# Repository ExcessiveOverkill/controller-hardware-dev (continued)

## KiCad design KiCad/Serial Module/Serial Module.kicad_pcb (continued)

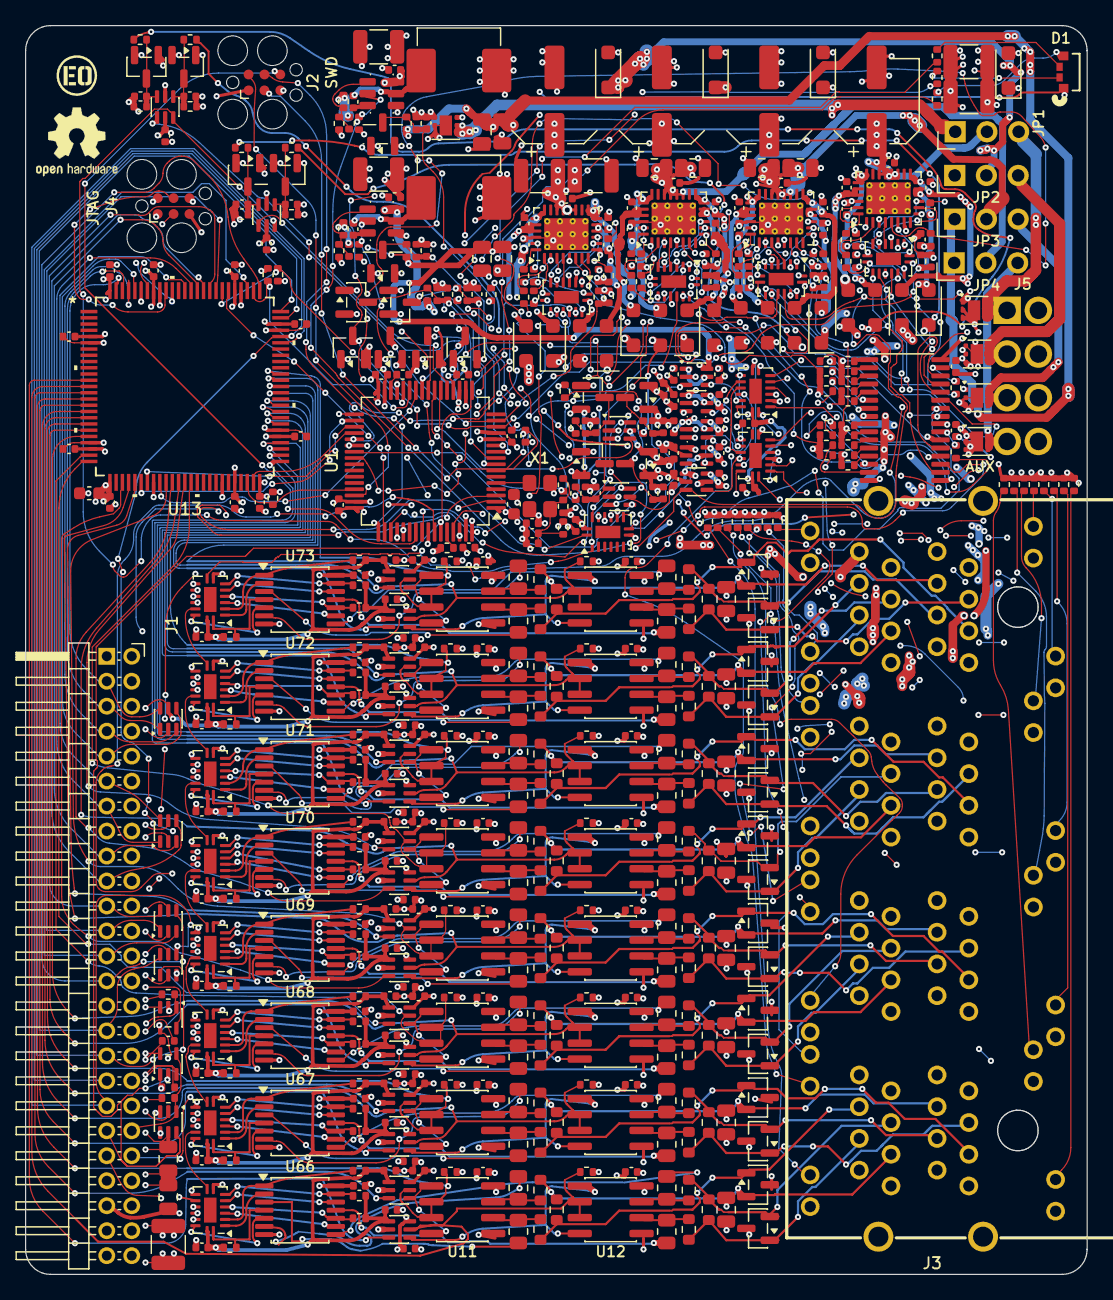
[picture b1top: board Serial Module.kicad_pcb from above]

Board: 4 copper layers, 85.0 x 100.0 mm, 564 parts (0 on the bottom side), 454 nets.

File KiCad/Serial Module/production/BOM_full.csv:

"Designator","Value","Footprint","Part number","Manufacturer","LCSC#","Qty","DNP"
"C1","4.7uf","Capacitor_SMD:C_0402_1005Metric","CC0402MRX5R6BB475","YAGEO","C469468","1",""
"C2,C4-C10,C15-C19,C25-C27,C30-C33,C38,C42,C43,C52,C53,C60-C67,C69-C88,C96-C109,C111-C113,C117-C131,C133,C134,C138,C139,C145-C152,C157,C158,C160-C165,C167-C172,C174-C188",".1uf","Capacitor_SMD:C_0402_1005Metric","CC0402KRX7R9BB104","YAGEO","C131394","126",""
"C3,C68","4.7uf","Capacitor_SMD:C_0603_1608Metric","CC0603KRX5R7BB475","YAGEO","C277476","2",""
"C11,C12,C46-C49,C115,C116,C136,C137,C140-C144,C159,C166,C173","22uf","Capacitor_SMD:C_0805_2012Metric","CC0805MKX5R8BB226","YAGEO","C784585","18",""
"C13,C24,C28,C35,C36,C110,C132","10uF","Capacitor_SMD:C_1210_3225Metric","CC1210KKX7R9BB106","YAGEO","C596319","7",""
"C14","2.2uf","Capacitor_SMD:C_0402_1005Metric","CC0402KRX5R6BB225","YAGEO","C326606","1",""
"C20-C23,C37,C39-C41,C50,C51,C54-C59","22nf","Capacitor_SMD:C_0402_1005Metric","CC0402KRX7R9BB223","YAGEO","C107026","16",""
"C29,C34,C44,C45","100uF","Capacitor_SMD:CP_Elec_6.3x7.7","JVJ50V100M6x8","jieerrui","C46550415","4",""
"C153-C156","10nf","Capacitor_SMD:C_0402_1005Metric","CC0402KRX7R9BB103","YAGEO","C60133","4",""
"D1","22-23C","footprints:22-23C_EVE","22-23C/R6GHBHW-C01/2C","Everlight","C181865","1",""
"D3,D4,D28-D35,D50-D55","BAT54SLT1G","Package_TO_SOT_SMD:SOT-23","LBAT54SLT1G","LRC","C12765","16",""
"D6,D7,D36-D49","SM712_SOT23","Package_TO_SOT_SMD:SOT-23","SM712","MDD(Microdiode Semiconductor)","C502564","16",""
"D8-D27","D_Schottky","Diode_SMD:D_SOD-123F","K24","GOODWORK","C908664","20",""
"D56,D57","TVS2700","Package_SON:WSON-6-1EP_2x2mm_P0.65mm_EP1x1.6mm","TVS2700DRVR","TI","C523797","2",""
"J1","Conn_02x25_Odd_Even","footprints:16x_modular_card","X4621WR-2x25I-C40D28","XKB Connection","C2883281","1",""
"J3","","footprints:RJ45-TH_HC-RJ45-059D-2X4-2-04","HC-RJ45-059D-2*4-2-04","HCTL","C46261621","1",""
"J5","Conn_02x04_Odd_Even","footprints:2x04_P3.5_KF2EDGSR","KF2EDGSR-3.5-2*4P","Cixi Kefa Elec","C2923262","1",""
"JP1-JP4","Jumper_3_Bridged12","footprints:PinHeader_1x03_P2.54mm_Vertical_Shunt12","PZ254V-11-03P","XFCN","C2937625","4",""
"JS1-JS4","Shunt 2.54mm","","2.54Short Circuit Cap Closed","BOOMELE","C100114","4",""
"L1,L5","6.8uH","Inductor_SMD:L_Changjiang_FXL0650","FXL0650-6R8-M","cjiang (Changjiang Microelectronics)","C475530","2",""
"R1,R2,R6,R8,R9,R30,R32,R34,R36,R38,R40,R42,R44,R256,R270,R287,R288","1k","Resistor_SMD:R_0402_1005Metric","RC0402FR-071KL","YAGEO","C106235","17",""
"R3-R5,R7,R24-R29,R31,R33,R35,R37,R39,R41,R43,R61-R63,R160,R161,R243,R244,R247,R248,R353-R421","10k","Resistor_SMD:R_0402_1005Metric","RC0402FR-0710KL","YAGEO","C60490","95",""
"R14-R17,R45-R60,R64-R67,R74-R77,R84-R87,R94-R97,R104-R107,R114-R117,R124-R127","470","Resistor_SMD:R_0402_1005Metric","RC0402FR-07470RL","YAGEO","C114877","48",""
"R18-R21,R68-R71,R78-R81,R88-R91,R98-R101,R108-R111,R118-R121,R128-R131","10","Resistor_SMD:R_0402_1005Metric","RC0402FR-0710RL","YAGEO","C138066","32",""
"R22,R23,R72,R73,R82,R83,R92,R93,R102,R103,R112,R113,R122,R123,R132,R133","137","Resistor_SMD:R_0603_1608Metric","0603WAF1370T5E","UNI-ROYAL","C22873","16",""
"R162,R245","100k","Resistor_SMD:R_0402_1005Metric","RC0402FR-07100KL","YAGEO","C60491","2",""
"R163","12.4k","Resistor_SMD:R_0402_1005Metric","RC0402FR-0712K4L","YAGEO","C138060","1",""
"R246","13.3k","Resistor_SMD:R_0402_1005Metric","RC0402FR-0713K3L","YAGEO","C274352","1",""
"R249-R252","330","Resistor_SMD:R_0402_1005Metric","RC0402FR-07330RL","YAGEO","C105875","4",""
"R253,R257,R262,R264,R271,R272,R275,R276","8.06k","Resistor_SMD:R_0402_1005Metric","RC0402FR-078K06L","YAGEO","C276278","8",""
"R254,R266,R279,R280","4.02k","Resistor_SMD:R_0402_1005Metric","RC0402FR-074K02L","YAGEO","C137968","4",""
"R255,R268,R283,R284","2k","Resistor_SMD:R_0402_1005Metric","RC0402FR-072KL","YAGEO","C60488","4",""
"U1","STM32F411RETx","Package_QFP:LQFP-64_10x10mm_P0.5mm","STM32F411RET6","STMicroelectronics","C94355","1",""
"U2-U6","D1213A-04S-7","Package_TO_SOT_SMD:SOT-363_SC-70-6","D1213A-04S-7-ES","ElecSuper","C41409235","5",""
"U7,U8","74LVC1G126","Package_TO_SOT_SMD:SOT-353_SC-70-5","74LVC1G126CT05ARCQ","GR","C48391411","2",""
"U9,U10,U16,U17,U28,U29,U32,U33,U36,U37,U40,U41,U44,U45,U48,U49,U88-U92","SN74LVC1T45DCK","Package_TO_SOT_SMD:SOT-363_SC-70-6","SN74LVC1T45DCKR","TI","C9382","21",""
"U11,U12,U26,U27,U30,U31,U34,U35,U38,U39,U42,U43,U46,U47,U50,U61","THVD1420DRL","Package_TO_SOT_SMD:SOT-583-8","THVD1420DRLR","TI","C3235555","16",""
"U13","LCMXO2-640HC-4TG100I","footprints:TQFP100_LAT","LCMXO2-640HC-4TG100I","Lattice","C5680157","1",""
"U14,U18,U20,U21,U51-U60,U84","74HC595","Package_DFN_QFN:DHVQFN-16-1EP_2.5x3.5mm_P0.5mm_EP1x2mm","74HC595BQ,115","Nexperia","C730243","15",""
"U15,U19,U22,U23","TPS274160BRLHR","Package_DFN_QFN:VQFN-28-1EP_4x5mm_P0.5mm_EP2.55x3.55mm_ThermalVias","TPS274160BRLHR","TI","C2797257","4",""
"U24,U25","74HCS596","Package_SO:TSSOP-16_4.4x5mm_P0.65mm","SN74HCS596QPWRQ1","TI","C2862662","2",""
"U65,U82","LMR51420YFDDCR","Package_TO_SOT_SMD:SOT-23-6","LMR51420YFDDCR","TI","C7296200","2",""
"U66-U73","74ACT125","Package_SO:TSSOP-14_4.4x5mm_P0.65mm","SN74ACT125PWR","TI","C52940839","8",""
"U83,U85-U87","74LVC1G3157","Package_TO_SOT_SMD:SOT-363_SC-70-6","SN74LVC1G3157DCKR","TI","C38663","4",""
"X1","25Mhz","Oscillator:Oscillator_SMD_Abracon_ASE-4Pin_3.2x2.5mm","SX3V25.000B20100F30TNN","SCTF","C5179998","1",""

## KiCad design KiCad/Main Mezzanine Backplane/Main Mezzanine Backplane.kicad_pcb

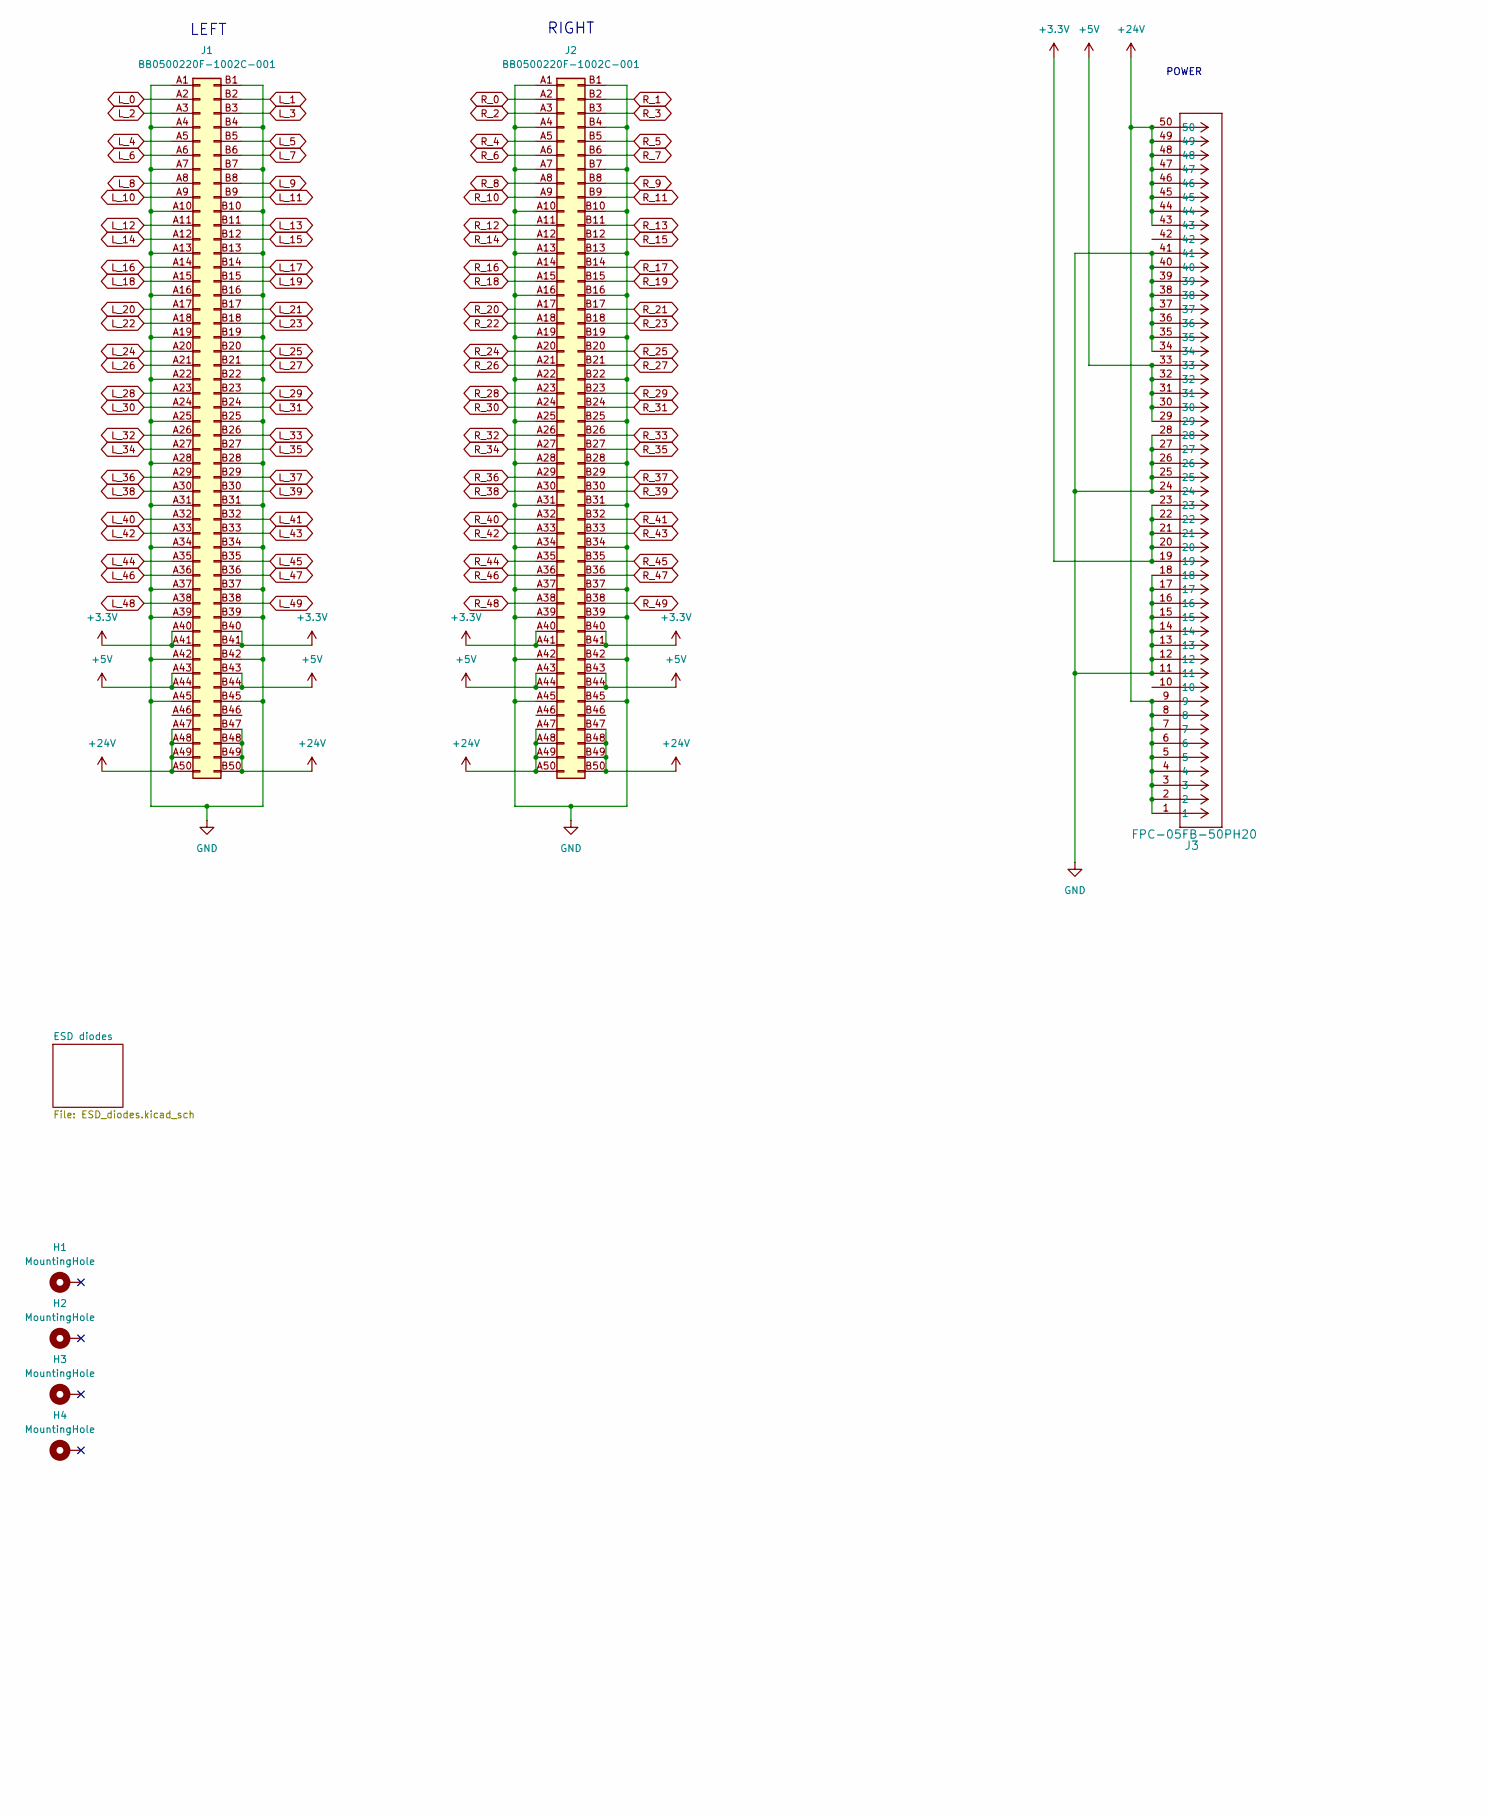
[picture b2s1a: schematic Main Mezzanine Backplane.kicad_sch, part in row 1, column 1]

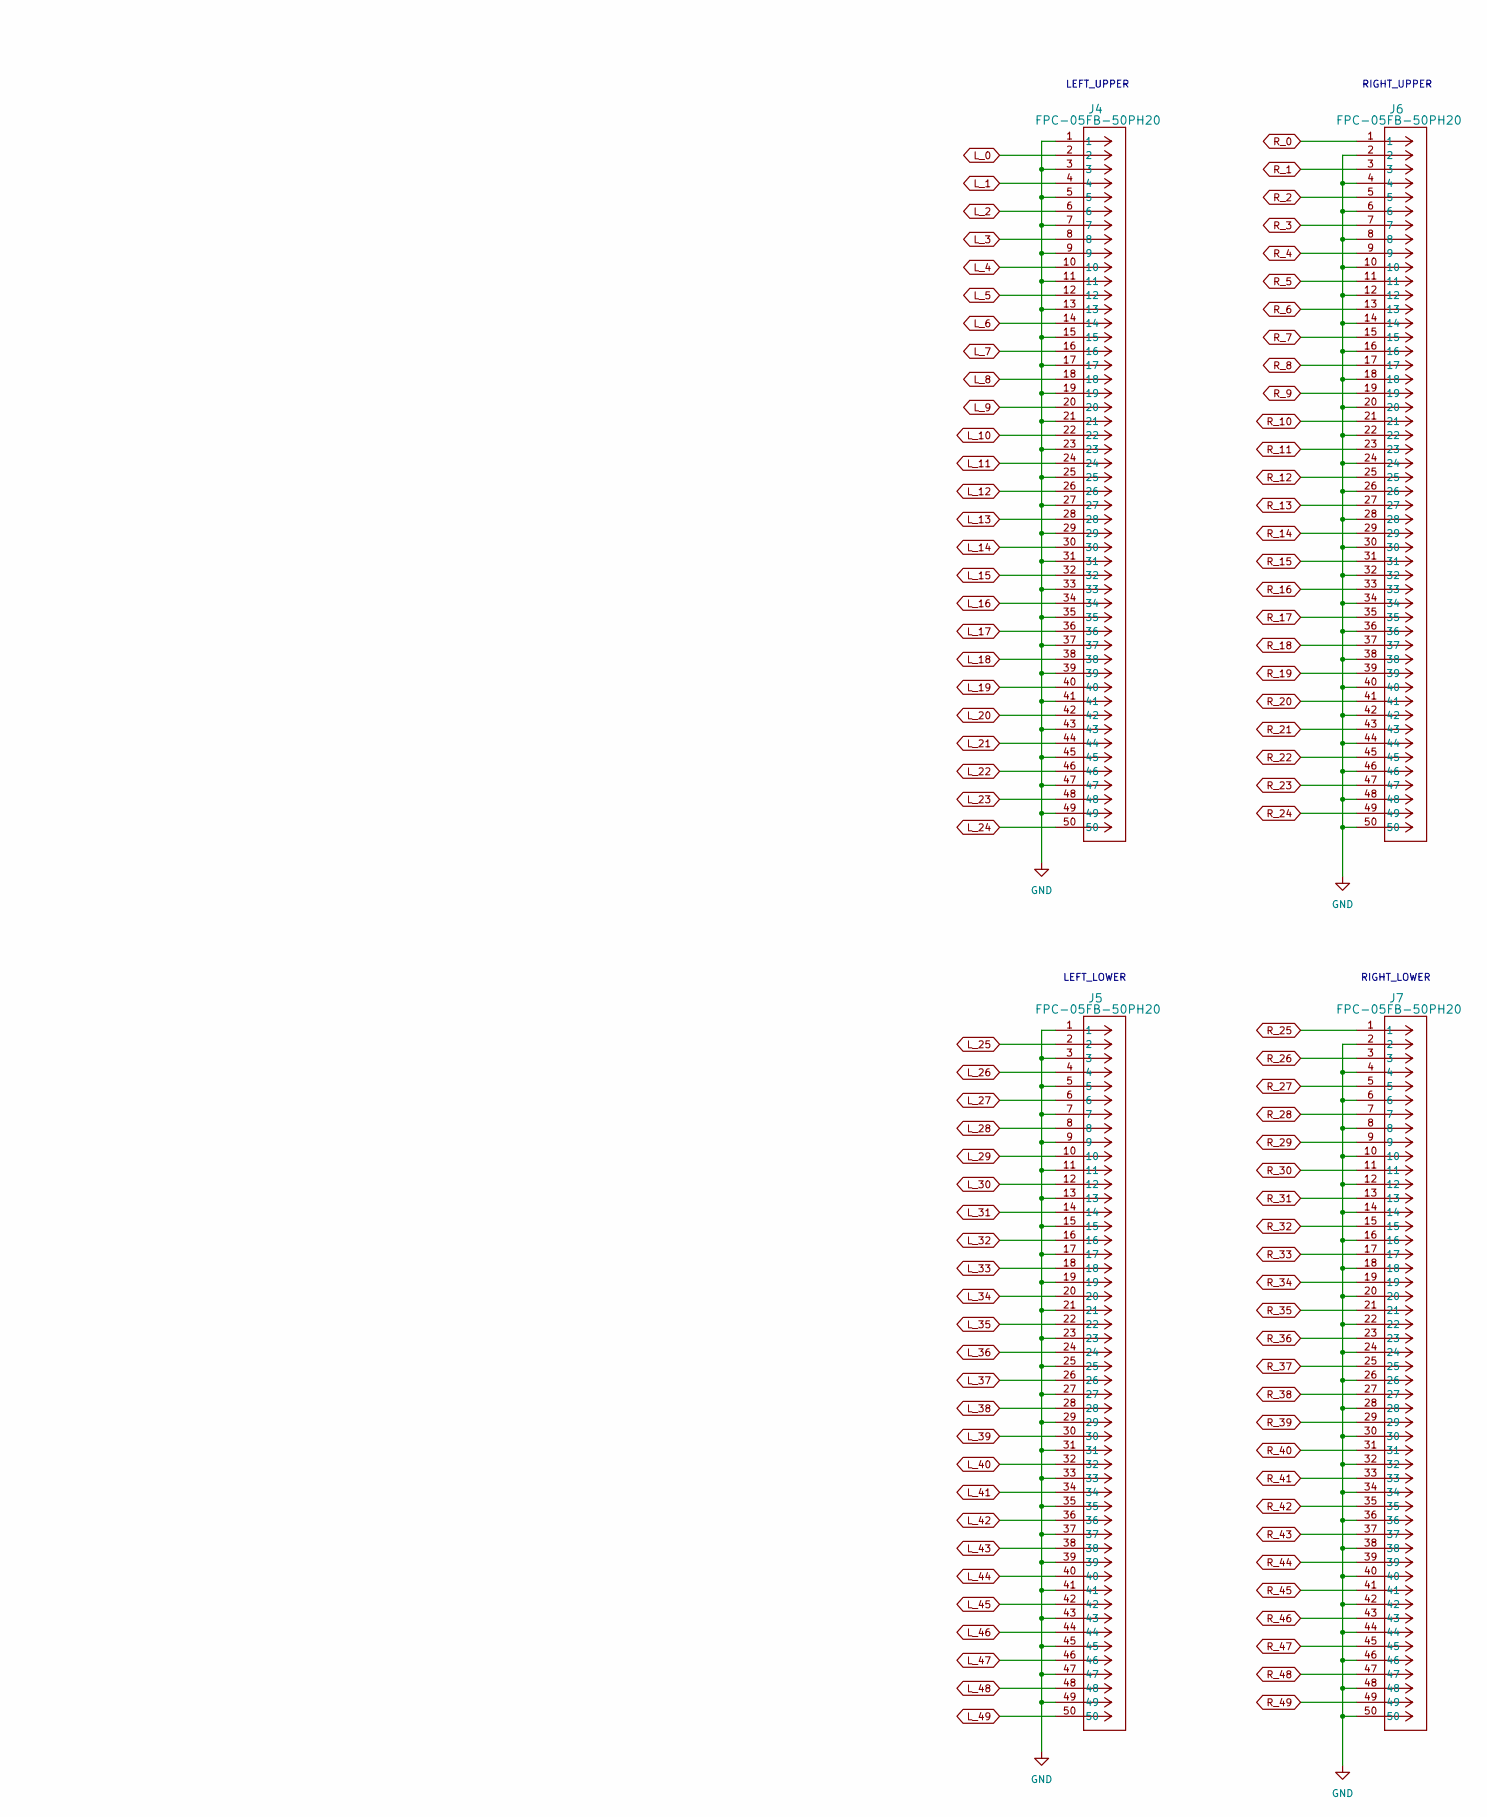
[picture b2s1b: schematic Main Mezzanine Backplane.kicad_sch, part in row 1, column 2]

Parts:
H1, H2, H3, H4: MountingHole; MountingHole_3.2mm_M3_Pad_TopBottom
J1, J2: BB0500220F-1002C-001; Part Number BB0500220F-1002C-001; LCSC# C42421167
J3, J4, J5, J6, J7: FPC-05FB-50PH20; CONN50_FPC-05FB-50PH20_XNP

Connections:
+3.3V: J1.A40, J1.A41, J1.B40, J1.B41, J2.A40, J2.A41, J2.B40, J2.B41, J3.19, J3.20, J3.21, J3.22, J3.23; also elsewhere on the board
+5V: J1.A43, J1.A44, J1.B43, J1.B44, J2.A43, J2.A44, J2.B43, J2.B44, J3.29, J3.30, J3.31, J3.32, J3.33
+24V: J1.A47, J1.A48, J1.A49, J1.A50, J1.B47, J1.B48, J1.B49, J1.B50, J2.A47, J2.A48, J2.A49, J2.A50, J2.B47, J2.B48, J2.B49, J2.B50, J3.1, J3.2, J3.3, J3.4, J3.5, J3.6, J3.7, J3.8, J3.9, J3.43, J3.44, J3.45, J3.46, J3.47, J3.48, J3.49, J3.50
GND: J1.A1, J1.A4, J1.A7, J1.A10, J1.A13, J1.A16, J1.A19, J1.A22, J1.A25, J1.A28, J1.A31, J1.A34, J1.A37, J1.A39, J1.A42, J1.A45, J1.B1, J1.B4, J1.B7, J1.B10, J1.B13, J1.B16, J1.B19, J1.B22, J1.B25, J1.B28, J1.B31, J1.B34, J1.B37, J1.B39, J1.B42, J1.B45, J2.A1, J2.A4, J2.A7, J2.A10, J2.A13, J2.A16, J2.A19, J2.A22, J2.A25, J2.A28, J2.A31, J2.A34, J2.A37, J2.A39, J2.A42, J2.A45, J2.B1, J2.B4, J2.B7, J2.B10, J2.B13, J2.B16, J2.B19, J2.B22, J2.B25, J2.B28, J2.B31, J2.B34, J2.B37, J2.B39, J2.B42, J2.B45, J3.11, J3.12, J3.13, J3.14, J3.15, J3.16, J3.17, J3.18, J3.24, J3.25, J3.26, J3.27, J3.28, J3.34, J3.35, J3.36, J3.37, J3.38, J3.39, J3.40, J3.41, J4.1, J4.3, J4.5, J4.7, J4.9, J4.11, J4.13, J4.15, J4.17, J4.19, J4.21, J4.23, J4.25, J4.27, J4.29, J4.31, J4.33, J4.35, J4.37, J4.39, J4.41, J4.43, J4.45, J4.47, J4.49, J5.1, J5.3, J5.5, J5.7, J5.9, J5.11, J5.13, J5.15, J5.17, J5.19, J5.21, J5.23, J5.25, J5.27, J5.29, J5.31, J5.33, J5.35, J5.37, J5.39, J5.41, J5.43, J5.45, J5.47, J5.49, J6.2, J6.4, J6.6, J6.8, J6.10, J6.12, J6.14, J6.16, J6.18, J6.20, J6.22, J6.24, J6.26, J6.28, J6.30, J6.32, J6.34, J6.36, J6.38, J6.40, J6.42, J6.44, J6.46, J6.48, J6.50, J7.2, J7.4, J7.6, J7.8, J7.10, J7.12, J7.14, J7.16, J7.18, J7.20, J7.22, J7.24, J7.26, J7.28, J7.30, J7.32, J7.34, J7.36, J7.38, J7.40, J7.42, J7.44, J7.46, J7.48, J7.50; also elsewhere on the board
L_0: J1.A2, J4.2; also elsewhere on the board
L_1: J1.B2, J4.4; also elsewhere on the board
L_2: J1.A3, J4.6; also elsewhere on the board
L_3: J1.B3, J4.8; also elsewhere on the board
L_4: J1.A5, J4.10; also elsewhere on the board
L_5: J1.B5, J4.12; also elsewhere on the board
L_6: J1.A6, J4.14; also elsewhere on the board
L_7: J1.B6, J4.16; also elsewhere on the board
L_8: J1.A8, J4.18; also elsewhere on the board
L_9: J1.B8, J4.20; also elsewhere on the board
L_10: J1.A9, J4.22; also elsewhere on the board
L_11: J1.B9, J4.24; also elsewhere on the board
L_12: J1.A11, J4.26; also elsewhere on the board
L_13: J1.B11, J4.28; also elsewhere on the board
L_14: J1.A12, J4.30; also elsewhere on the board
L_15: J1.B12, J4.32; also elsewhere on the board
L_16: J1.A14, J4.34; also elsewhere on the board
L_17: J1.B14, J4.36; also elsewhere on the board
L_18: J1.A15, J4.38; also elsewhere on the board
L_19: J1.B15, J4.40; also elsewhere on the board
L_20: J1.A17, J4.42; also elsewhere on the board
L_21: J1.B17, J4.44; also elsewhere on the board
L_22: J1.A18, J4.46; also elsewhere on the board
L_23: J1.B18, J4.48; also elsewhere on the board
L_24: J1.A20, J4.50; also elsewhere on the board
L_25: J1.B20, J5.2; also elsewhere on the board
L_26: J1.A21, J5.4; also elsewhere on the board
L_27: J1.B21, J5.6; also elsewhere on the board
L_28: J1.A23, J5.8; also elsewhere on the board
L_29: J1.B23, J5.10; also elsewhere on the board
L_30: J1.A24, J5.12; also elsewhere on the board
L_31: J1.B24, J5.14; also elsewhere on the board
L_32: J1.A26, J5.16; also elsewhere on the board
L_33: J1.B26, J5.18; also elsewhere on the board
L_34: J1.A27, J5.20; also elsewhere on the board
L_35: J1.B27, J5.22; also elsewhere on the board
L_36: J1.A29, J5.24; also elsewhere on the board
L_37: J1.B29, J5.26; also elsewhere on the board
L_38: J1.A30, J5.28; also elsewhere on the board
L_39: J1.B30, J5.30; also elsewhere on the board
L_40: J1.A32, J5.32; also elsewhere on the board
L_41: J1.B32, J5.34; also elsewhere on the board
L_42: J1.A33, J5.36; also elsewhere on the board
L_43: J1.B33, J5.38; also elsewhere on the board
L_44: J1.A35, J5.40; also elsewhere on the board
L_45: J1.B35, J5.42; also elsewhere on the board
L_46: J1.A36, J5.44; also elsewhere on the board
L_47: J1.B36, J5.46; also elsewhere on the board
L_48: J1.A38, J5.48; also elsewhere on the board
L_49: J1.B38, J5.50; also elsewhere on the board
R_0: J2.A2, J6.1; also elsewhere on the board
R_1: J2.B2, J6.3; also elsewhere on the board
R_2: J2.A3, J6.5; also elsewhere on the board
R_3: J2.B3, J6.7; also elsewhere on the board
R_4: J2.A5, J6.9; also elsewhere on the board
R_5: J2.B5, J6.11; also elsewhere on the board
R_6: J2.A6, J6.13; also elsewhere on the board
R_7: J2.B6, J6.15; also elsewhere on the board
R_8: J2.A8, J6.17; also elsewhere on the board
R_9: J2.B8, J6.19; also elsewhere on the board
R_10: J2.A9, J6.21; also elsewhere on the board
R_11: J2.B9, J6.23; also elsewhere on the board
R_12: J2.A11, J6.25; also elsewhere on the board
R_13: J2.B11, J6.27; also elsewhere on the board
R_14: J2.A12, J6.29; also elsewhere on the board
R_15: J2.B12, J6.31; also elsewhere on the board
R_16: J2.A14, J6.33; also elsewhere on the board
R_17: J2.B14, J6.35; also elsewhere on the board
R_18: J2.A15, J6.37; also elsewhere on the board
R_19: J2.B15, J6.39; also elsewhere on the board
R_20: J2.A17, J6.41; also elsewhere on the board
R_21: J2.B17, J6.43; also elsewhere on the board
R_22: J2.A18, J6.45; also elsewhere on the board
R_23: J2.B18, J6.47; also elsewhere on the board
R_24: J2.A20, J6.49; also elsewhere on the board
R_25: J2.B20, J7.1; also elsewhere on the board
R_26: J2.A21, J7.3; also elsewhere on the board
R_27: J2.B21, J7.5; also elsewhere on the board
R_28: J2.A23, J7.7; also elsewhere on the board
R_29: J2.B23, J7.9; also elsewhere on the board
R_30: J2.A24, J7.11; also elsewhere on the board
R_31: J2.B24, J7.13; also elsewhere on the board
R_32: J2.A26, J7.15; also elsewhere on the board
R_33: J2.B26, J7.17; also elsewhere on the board
R_34: J2.A27, J7.19; also elsewhere on the board
R_35: J2.B27, J7.21; also elsewhere on the board
R_36: J2.A29, J7.23; also elsewhere on the board
R_37: J2.B29, J7.25; also elsewhere on the board
R_38: J2.A30, J7.27; also elsewhere on the board
R_39: J2.B30, J7.29; also elsewhere on the board
R_40: J2.A32, J7.31; also elsewhere on the board
R_41: J2.B32, J7.33; also elsewhere on the board
R_42: J2.A33, J7.35; also elsewhere on the board
R_43: J2.B33, J7.37; also elsewhere on the board
R_44: J2.A35, J7.39; also elsewhere on the board
R_45: J2.B35, J7.41; also elsewhere on the board
R_46: J2.A36, J7.43; also elsewhere on the board
R_47: J2.B36, J7.45; also elsewhere on the board
R_48: J2.A38, J7.47; also elsewhere on the board
R_49: J2.B38, J7.49; also elsewhere on the board

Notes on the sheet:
LEFT_UPPER
POWER
LEFT_LOWER
LEFT
RIGHT_UPPER
RIGHT
RIGHT_LOWER

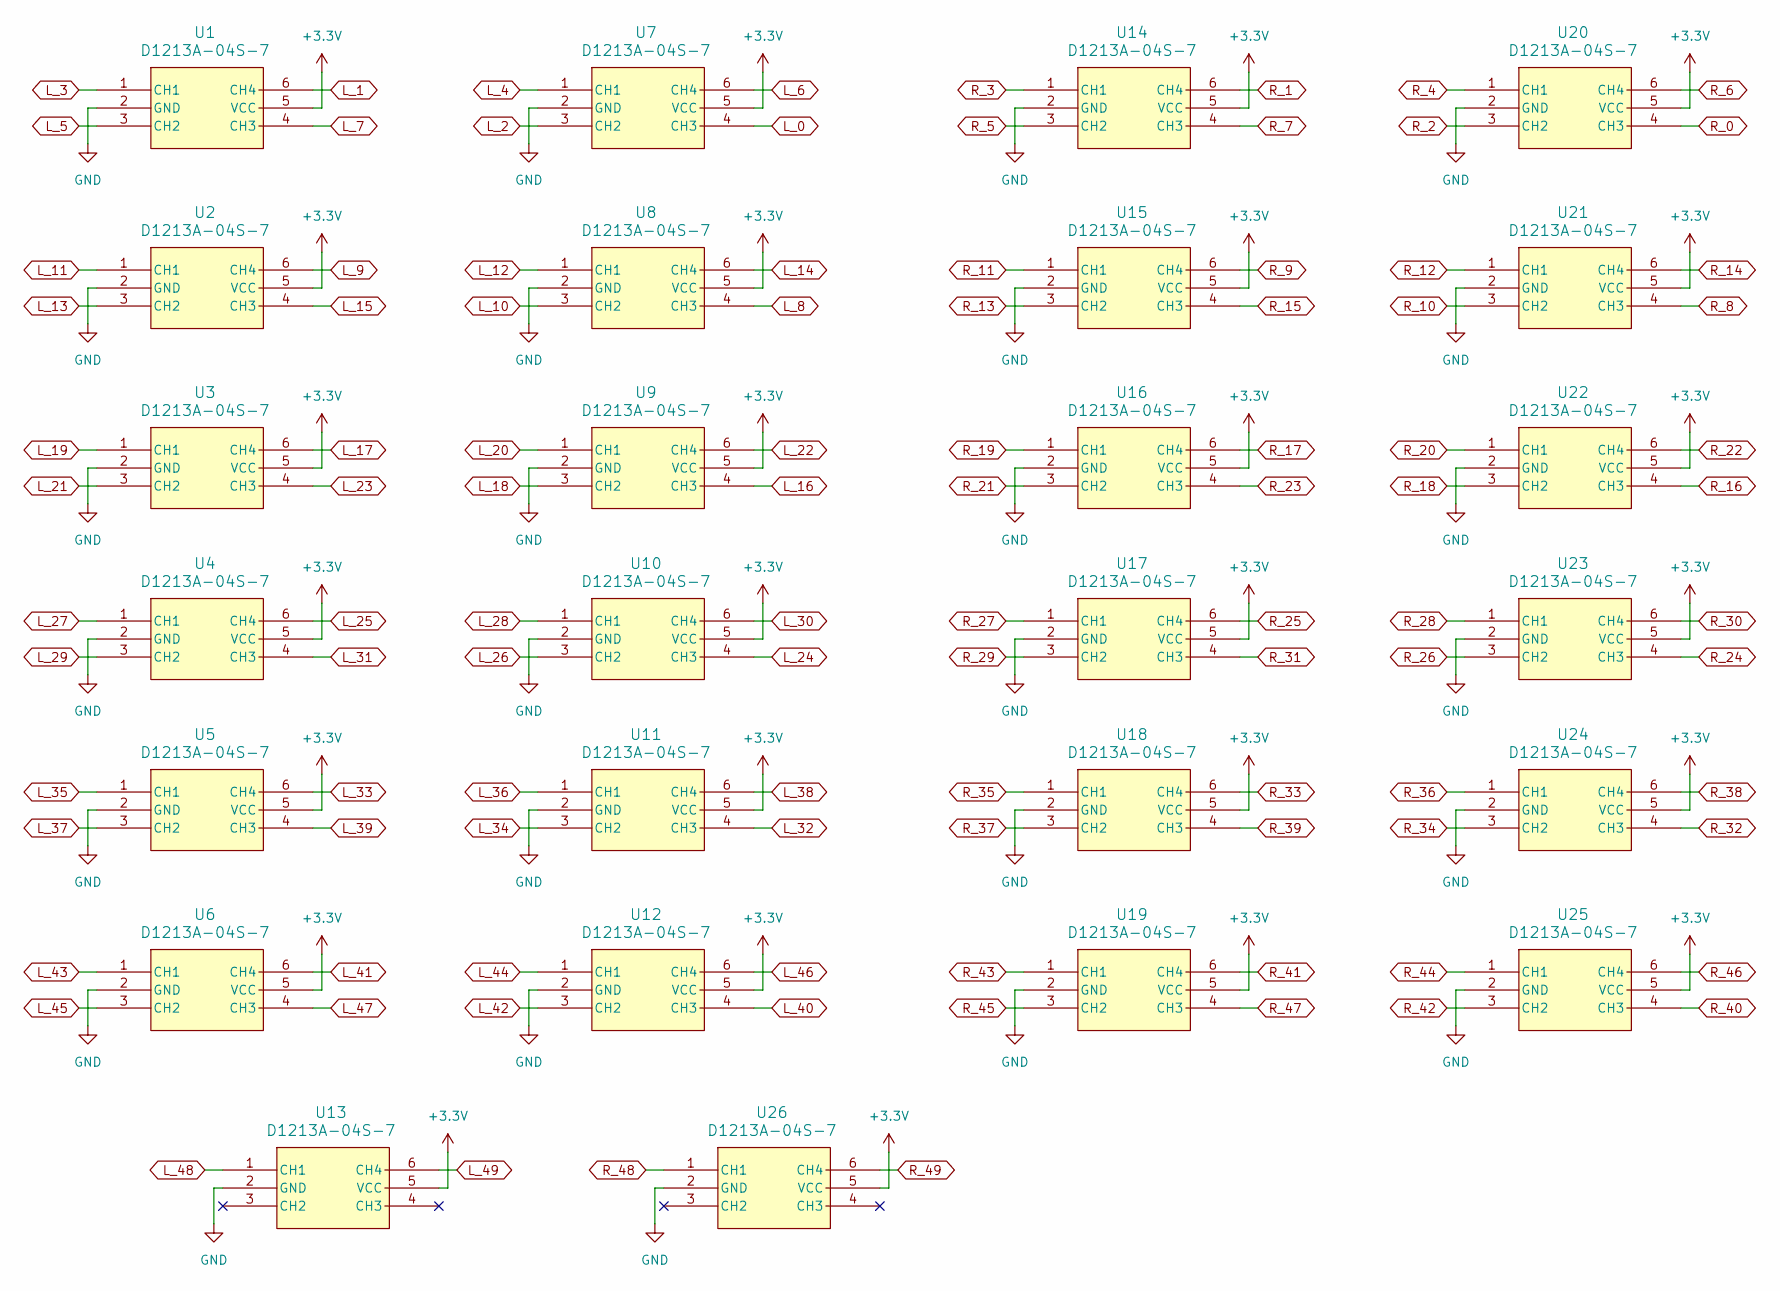
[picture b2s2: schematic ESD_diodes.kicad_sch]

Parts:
U1, U2, U3, U4, U5, U6, U7, U8, U9, U10, U11, U12, U13, U14, U15, U16, U17, U18, U19, U20, U21, U22, U23, U24, U25, U26: D1213A-04S-7; SOT-363_DIO; Part Number D1213A-04S-7-ES; LCSC# C41409235

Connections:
+3.3V: U1.5 (VCC), U2.5 (VCC), U3.5 (VCC), U4.5 (VCC), U5.5 (VCC), U6.5 (VCC), U7.5 (VCC), U8.5 (VCC), U9.5 (VCC), U10.5 (VCC), U11.5 (VCC), U12.5 (VCC), U13.5 (VCC), U14.5 (VCC), U15.5 (VCC), U16.5 (VCC), U17.5 (VCC), U18.5 (VCC), U19.5 (VCC), U20.5 (VCC), U21.5 (VCC), U22.5 (VCC), U23.5 (VCC), U24.5 (VCC), U25.5 (VCC), U26.5 (VCC); also elsewhere on the board
GND: U1.2 (GND), U2.2 (GND), U3.2 (GND), U4.2 (GND), U5.2 (GND), U6.2 (GND), U7.2 (GND), U8.2 (GND), U9.2 (GND), U10.2 (GND), U11.2 (GND), U12.2 (GND), U13.2 (GND), U14.2 (GND), U15.2 (GND), U16.2 (GND), U17.2 (GND), U18.2 (GND), U19.2 (GND), U20.2 (GND), U21.2 (GND), U22.2 (GND), U23.2 (GND), U24.2 (GND), U25.2 (GND), U26.2 (GND); also elsewhere on the board
L_0: U7.4 (CH3); also elsewhere on the board
L_1: U1.6 (CH4); also elsewhere on the board
L_2: U7.3 (CH2); also elsewhere on the board
L_3: U1.1 (CH1); also elsewhere on the board
L_4: U7.1 (CH1); also elsewhere on the board
L_5: U1.3 (CH2); also elsewhere on the board
L_6: U7.6 (CH4); also elsewhere on the board
L_7: U1.4 (CH3); also elsewhere on the board
L_8: U8.4 (CH3); also elsewhere on the board
L_9: U2.6 (CH4); also elsewhere on the board
L_10: U8.3 (CH2); also elsewhere on the board
L_11: U2.1 (CH1); also elsewhere on the board
L_12: U8.1 (CH1); also elsewhere on the board
L_13: U2.3 (CH2); also elsewhere on the board
L_14: U8.6 (CH4); also elsewhere on the board
L_15: U2.4 (CH3); also elsewhere on the board
L_16: U9.4 (CH3); also elsewhere on the board
L_17: U3.6 (CH4); also elsewhere on the board
L_18: U9.3 (CH2); also elsewhere on the board
L_19: U3.1 (CH1); also elsewhere on the board
L_20: U9.1 (CH1); also elsewhere on the board
L_21: U3.3 (CH2); also elsewhere on the board
L_22: U9.6 (CH4); also elsewhere on the board
L_23: U3.4 (CH3); also elsewhere on the board
L_24: U10.4 (CH3); also elsewhere on the board
L_25: U4.6 (CH4); also elsewhere on the board
L_26: U10.3 (CH2); also elsewhere on the board
L_27: U4.1 (CH1); also elsewhere on the board
L_28: U10.1 (CH1); also elsewhere on the board
L_29: U4.3 (CH2); also elsewhere on the board
L_30: U10.6 (CH4); also elsewhere on the board
L_31: U4.4 (CH3); also elsewhere on the board
L_32: U11.4 (CH3); also elsewhere on the board
L_33: U5.6 (CH4); also elsewhere on the board
L_34: U11.3 (CH2); also elsewhere on the board
L_35: U5.1 (CH1); also elsewhere on the board
L_36: U11.1 (CH1); also elsewhere on the board
L_37: U5.3 (CH2); also elsewhere on the board
L_38: U11.6 (CH4); also elsewhere on the board
L_39: U5.4 (CH3); also elsewhere on the board
L_40: U12.4 (CH3); also elsewhere on the board
L_41: U6.6 (CH4); also elsewhere on the board
L_42: U12.3 (CH2); also elsewhere on the board
L_43: U6.1 (CH1); also elsewhere on the board
L_44: U12.1 (CH1); also elsewhere on the board
L_45: U6.3 (CH2); also elsewhere on the board
L_46: U12.6 (CH4); also elsewhere on the board
L_47: U6.4 (CH3); also elsewhere on the board
L_48: U13.1 (CH1); also elsewhere on the board
L_49: U13.6 (CH4); also elsewhere on the board
R_0: U20.4 (CH3); also elsewhere on the board
R_1: U14.6 (CH4); also elsewhere on the board
R_2: U20.3 (CH2); also elsewhere on the board
R_3: U14.1 (CH1); also elsewhere on the board
R_4: U20.1 (CH1); also elsewhere on the board
R_5: U14.3 (CH2); also elsewhere on the board
R_6: U20.6 (CH4); also elsewhere on the board
R_7: U14.4 (CH3); also elsewhere on the board
R_8: U21.4 (CH3); also elsewhere on the board
R_9: U15.6 (CH4); also elsewhere on the board
R_10: U21.3 (CH2); also elsewhere on the board
R_11: U15.1 (CH1); also elsewhere on the board
R_12: U21.1 (CH1); also elsewhere on the board
R_13: U15.3 (CH2); also elsewhere on the board
R_14: U21.6 (CH4); also elsewhere on the board
R_15: U15.4 (CH3); also elsewhere on the board
R_16: U22.4 (CH3); also elsewhere on the board
R_17: U16.6 (CH4); also elsewhere on the board
R_18: U22.3 (CH2); also elsewhere on the board
R_19: U16.1 (CH1); also elsewhere on the board
R_20: U22.1 (CH1); also elsewhere on the board
R_21: U16.3 (CH2); also elsewhere on the board
R_22: U22.6 (CH4); also elsewhere on the board
R_23: U16.4 (CH3); also elsewhere on the board
R_24: U23.4 (CH3); also elsewhere on the board
R_25: U17.6 (CH4); also elsewhere on the board
R_26: U23.3 (CH2); also elsewhere on the board
R_27: U17.1 (CH1); also elsewhere on the board
R_28: U23.1 (CH1); also elsewhere on the board
R_29: U17.3 (CH2); also elsewhere on the board
R_30: U23.6 (CH4); also elsewhere on the board
R_31: U17.4 (CH3); also elsewhere on the board
R_32: U24.4 (CH3); also elsewhere on the board
R_33: U18.6 (CH4); also elsewhere on the board
R_34: U24.3 (CH2); also elsewhere on the board
R_35: U18.1 (CH1); also elsewhere on the board
R_36: U24.1 (CH1); also elsewhere on the board
R_37: U18.3 (CH2); also elsewhere on the board
R_38: U24.6 (CH4); also elsewhere on the board
R_39: U18.4 (CH3); also elsewhere on the board
R_40: U25.4 (CH3); also elsewhere on the board
R_41: U19.6 (CH4); also elsewhere on the board
R_42: U25.3 (CH2); also elsewhere on the board
R_43: U19.1 (CH1); also elsewhere on the board
R_44: U25.1 (CH1); also elsewhere on the board
R_45: U19.3 (CH2); also elsewhere on the board
R_46: U25.6 (CH4); also elsewhere on the board
R_47: U19.4 (CH3); also elsewhere on the board
R_48: U26.1 (CH1); also elsewhere on the board
R_49: U26.6 (CH4); also elsewhere on the board

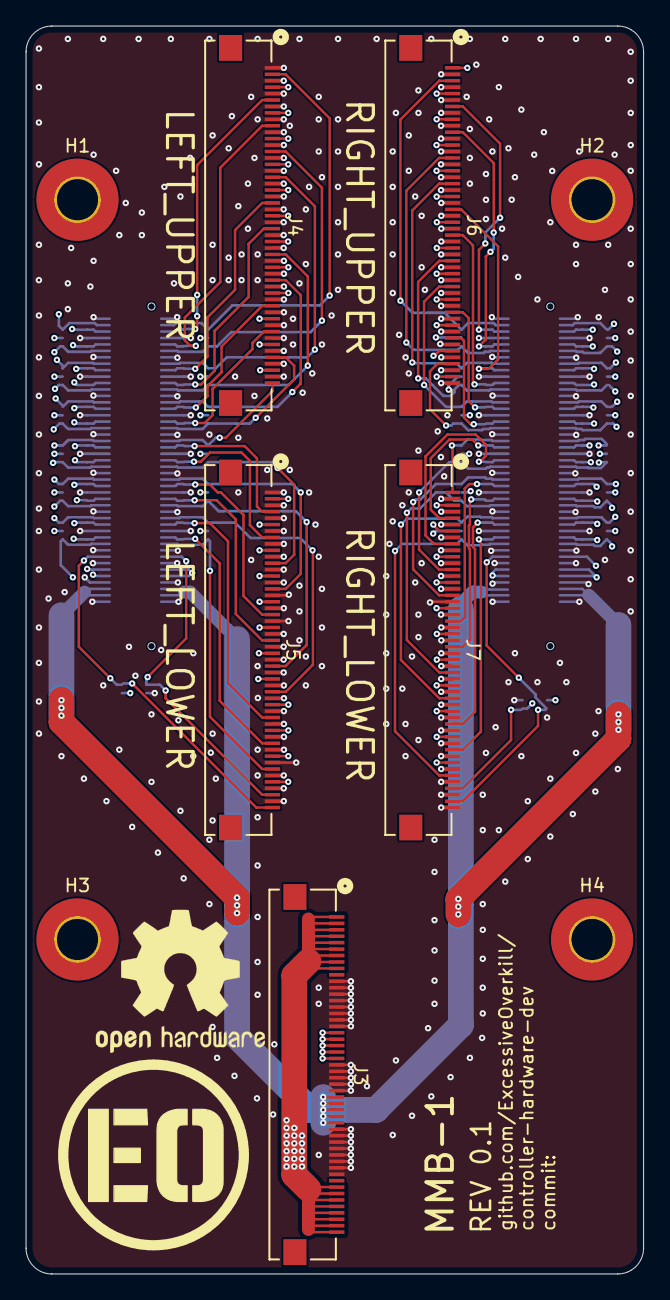
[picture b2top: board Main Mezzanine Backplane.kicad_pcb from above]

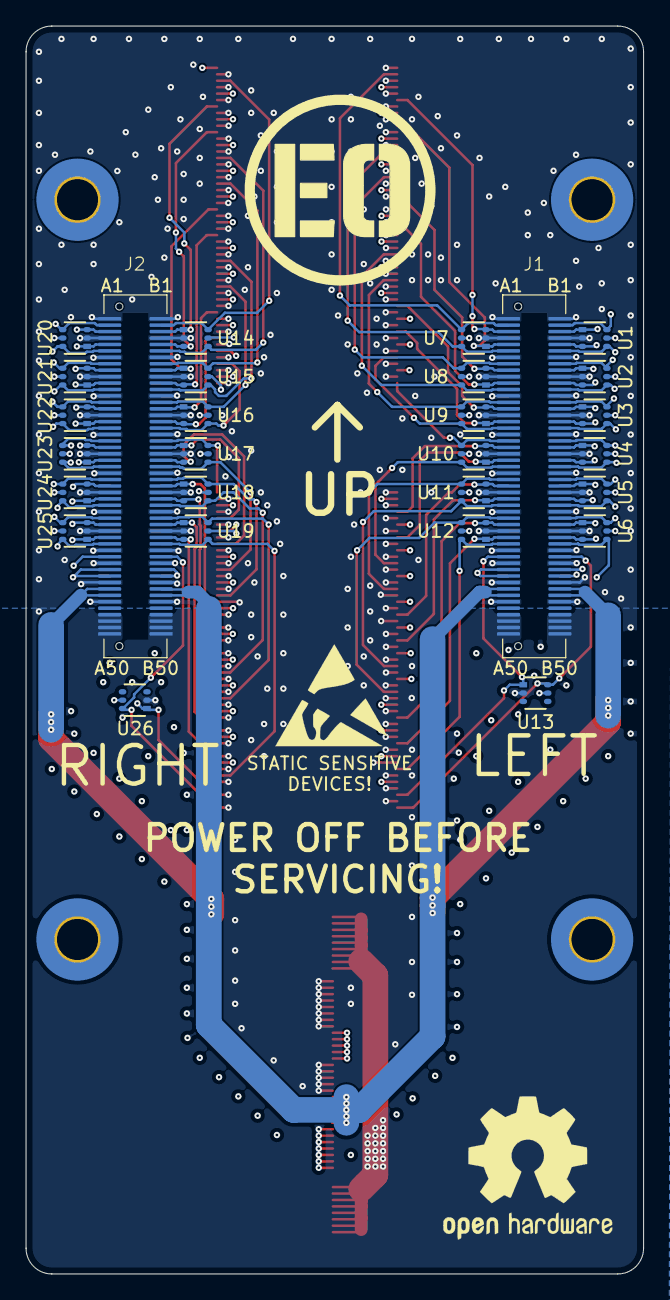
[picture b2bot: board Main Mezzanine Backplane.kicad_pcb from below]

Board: 4 copper layers, 48.0 x 97.0 mm, 37 parts (28 on the bottom side), 104 nets.
